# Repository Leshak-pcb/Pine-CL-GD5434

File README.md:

# Pine-CL-GD5434
CL-GD5434-based ISA VGA card.
Tested, works, but may still contain minor errors. Feature connector and 64k rom option are not tested yet.
Notes:
1) R1-R5 are configuration resistors, install R2 & R4 for fast DRAM, R2 & R3 for slow DRAM. Check CL-GD543x databook if you need more info.
2) U10 - optional, provides DD2B support (works with generic PCI BIOS).
3) FB1-F1-D2-C68 - DDC monitor power, remove if not using U10. D2 - BAT54 or equivalent, F1 - 200mA poly fuse.
4) U11 - optional, 93C46 used to store video modes supported by your monitor.
5) U12, U13 - optional, ESD & hot-plug protection.
6) C90-C92 - 10uF - 47uF 6.3V+
7) D1 can be replaced with 1n4148

Creative Commons Attribution-ShareAlike 4.0 International License. See https://creativecommons.org/licenses/by-sa/4.0/.

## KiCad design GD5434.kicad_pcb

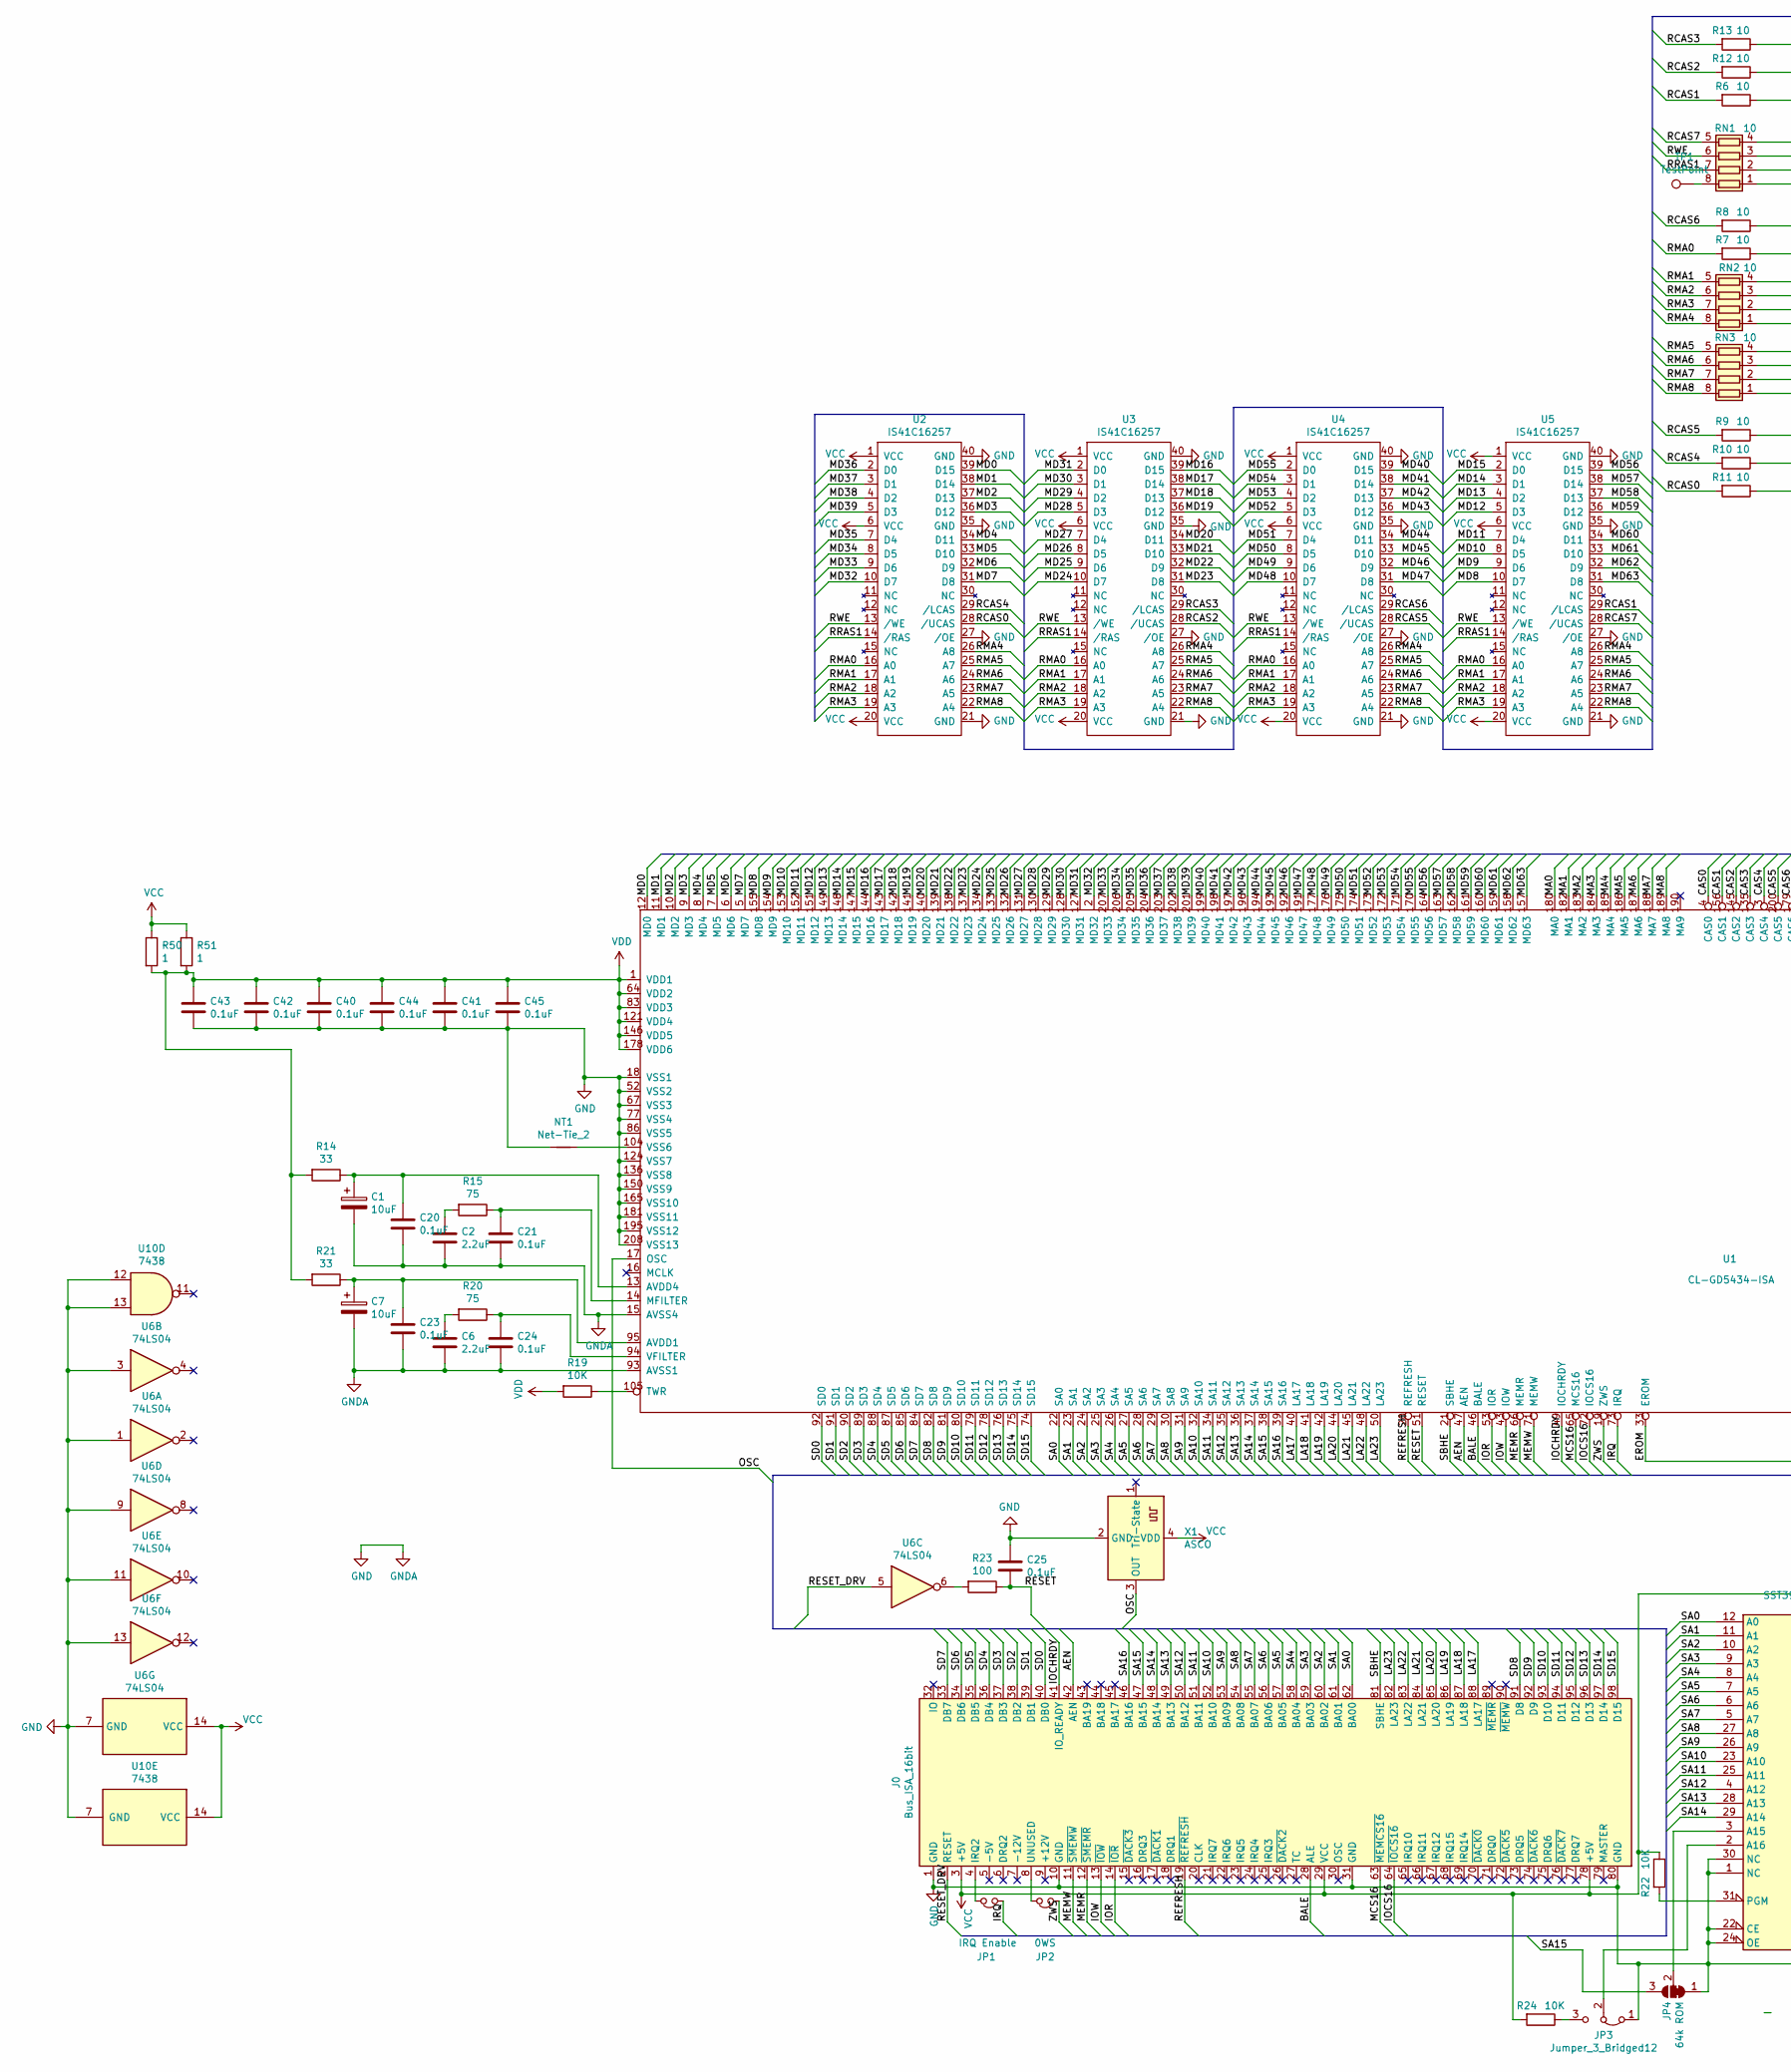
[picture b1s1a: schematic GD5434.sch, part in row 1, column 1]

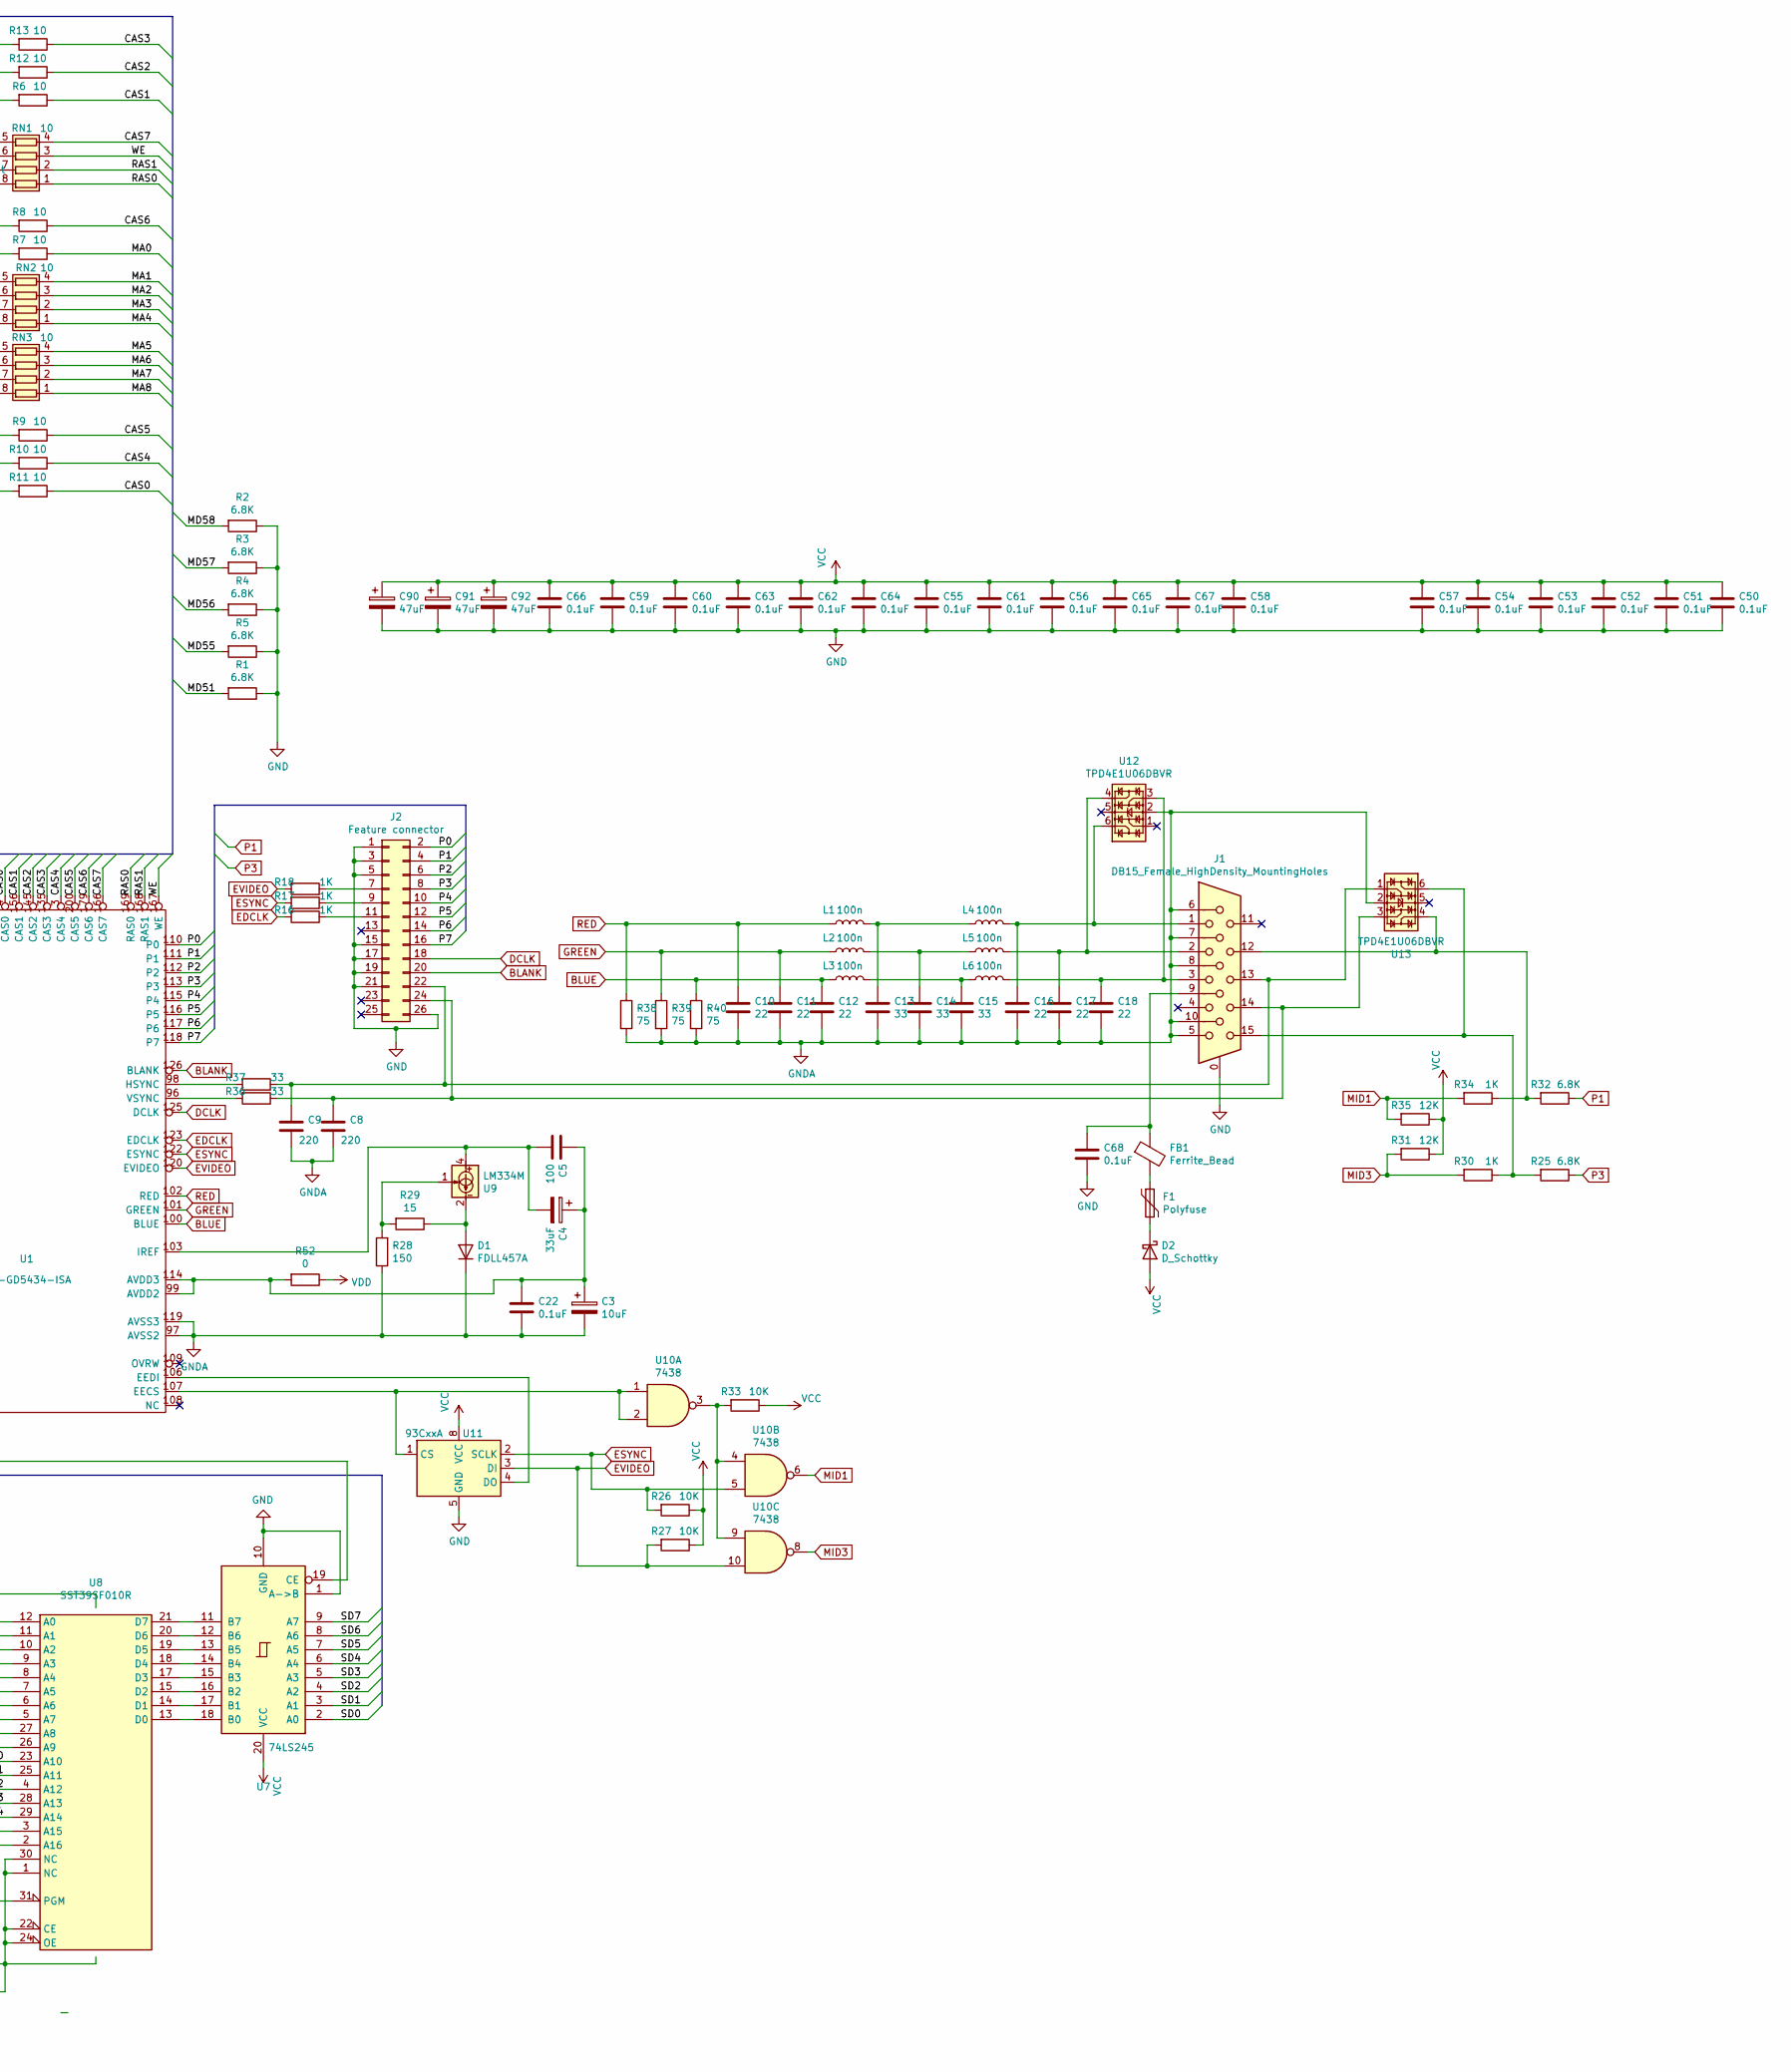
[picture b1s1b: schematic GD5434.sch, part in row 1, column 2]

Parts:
C1, C3, C7: 10uF; CP_Elec_5x5.8
C2, C6: 2.2uF; C_0805_2012Metric_Pad1.15x1.40mm_HandSolder
C4: 33uF; C_Elec_5x5.8
C5: 100; C_0805_2012Metric_Pad1.15x1.40mm_HandSolder
C8, C9: 220; C_0805_2012Metric_Pad1.15x1.40mm_HandSolder
C10, C11, C12, C16, C17, C18: 22; C_0805_2012Metric_Pad1.15x1.40mm_HandSolder
C13, C14, C15: 33; C_0805_2012Metric_Pad1.15x1.40mm_HandSolder
C20, C21, C22, C23, C24, C25, C50, C51, C52, C53, C54, C55, C56, C57, C58, C59, C60, C61, C62, C63, C64, C65, C66, C67, C68: 0.1uF; C_0805_2012Metric_Pad1.15x1.40mm_HandSolder
C40, C41, C42, C43, C44, C45: 0.1uF; C_0603_1608Metric_Pad1.05x0.95mm_HandSolder
C90, C91, C92: 47uF; CP_Radial_D5.0mm_P2.00mm
D1: FDLL457A; D_MiniMELF_Handsoldering
D2: D_Schottky; D_SOT-23_ANK
F1: Polyfuse; Fuse_0805_2012Metric_Pad1.15x1.40mm_HandSolder
FB1: Ferrite_Bead; L_0805_2012Metric_Pad1.15x1.40mm_HandSolder
J0: Bus_ISA_16bit; BUS_AT
J1: DB15_Female_HighDensity_MountingHoles; DSUB-15-HD_Female_Horizontal_P2.29x2.54mm
J2: Feature connector; IDC-Header_2x13_P2.54mm_Vertical
JP1: IRQ Enable; PinHeader_1x02_P2.54mm_Vertical
JP2: 0WS; PinHeader_1x02_P2.54mm_Vertical
JP3: Jumper_3_Bridged12; PinHeader_1x03_P2.54mm_Vertical
JP4: 64k ROM; SolderJumper-3_P1.3mm_Bridged12_RoundedPad1.0x1.5mm_NumberL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
L1, L2, L3, L4, L5, L6: 100n; L_0805_2012Metric_Pad1.15x1.40mm_HandSolder
NT1: Net-Tie_2; NetTie-2_SMD_Pad0.5mm
R1, R2, R3, R4, R5, R25, R32: 6.8K; R_0805_2012Metric_Pad1.15x1.40mm_HandSolder
R6, R9, R10, R11, R12: 10; R_0603_1608Metric_Pad1.05x0.95mm_HandSolder
R7, R8, R13: 10; R_0402_1005Metric
R14, R21, R36, R37: 33; R_0805_2012Metric_Pad1.15x1.40mm_HandSolder
R15, R20, R38, R39, R40: 75; R_0805_2012Metric_Pad1.15x1.40mm_HandSolder
R16, R17, R18, R30, R34: 1K; R_0805_2012Metric_Pad1.15x1.40mm_HandSolder
R19, R22, R24, R26, R27, R33: 10K; R_0805_2012Metric_Pad1.15x1.40mm_HandSolder
R23: 100; R_0805_2012Metric_Pad1.15x1.40mm_HandSolder
R28: 150; R_0805_2012Metric_Pad1.15x1.40mm_HandSolder
R29: 15; R_0805_2012Metric_Pad1.15x1.40mm_HandSolder
R31, R35: 12K; R_0805_2012Metric_Pad1.15x1.40mm_HandSolder
R50, R51: 1; R_1206_3216Metric_Pad1.42x1.75mm_HandSolder
R52: 0; R_0805_2012Metric_Pad1.15x1.40mm_HandSolder
RN1, RN2, RN3: 10; R_Array_Concave_4x0603
TP1: TestPoint; TestPoint_Pad_D1.0mm
U1: CL-GD5434-ISA; PQFP-208_28x28mm_P0.5mm
U2, U3, U4, U5: IS41C16257; SOJ-40-Socket-LongPads
U6: 74LS04; SO-14_5.3x10.2mm_P1.27mm
U7: 74LS245; SOIC-20W_7.5x12.8mm_P1.27mm
U8: SST39SF010R; PLCC-32_THT-Socket
U9: LM334M; SOIC-8_3.9x4.9mm_P1.27mm
U10: 7438; SOIC-14_3.9x8.7mm_P1.27mm
U11: 93CxxA; SOIC-8_3.9x4.9mm_P1.27mm
U12, U13: TPD4E1U06DBVR; SOT-23-6_Handsoldering
X1: ASCO; Oscillator_SMD_Abracon_ASV-4Pin_7.0x5.1mm_HandSoldering

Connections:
/AEN: J0.42 (AEN), U1.47 (AEN)
/BALE: J0.28 (ALE), U1.46 (BALE)
/CAS0: R11.1, U1.4 (CAS0)
/CAS1: R6.1, U1.156 (CAS1)
/CAS2: R12.1, U1.145 (CAS2)
/CAS3: R13.1, U1.135 (CAS3)
/CAS4: R10.1, U1.3 (CAS4)
/CAS5: R9.1, U1.200 (CAS5)
/CAS6: R8.1, U1.179 (CAS6)
/CAS7: RN1.4 (R4.1), U1.166 (CAS7)
/EROM: U1.33 (EROM), U7.19 (CE)
/IOCHRDY: J0.41 (IO_READY), U1.49 (IOCHRDY)
/IOCS16: J0.64 (~IOCS16), U1.72 (IOCS16)
/IOR: J0.14 (~IOR), U1.53 (IOR)
/IOW: J0.13 (~IOW), U1.43 (IOW)
/IRQ: JP1.1, U1.73 (IRQ)
/LA17: J0.88 (LA17), U1.40 (LA17)
/LA18: J0.87 (LA18), U1.41 (LA18)
/LA19: J0.86 (LA19), U1.42 (LA19)
/LA20: J0.85 (LA20), U1.44 (LA20)
/LA21: J0.84 (LA21), U1.45 (LA21)
/LA22: J0.83 (LA22), U1.48 (LA22)
/LA23: J0.82 (LA23), U1.50 (LA23)
/MA0: R7.1, U1.180 (MA0)
/MA1: RN2.4 (R4.1), U1.182 (MA1)
/MA2: RN2.3 (R3.1), U1.183 (MA2)
/MA3: RN2.2 (R2.1), U1.184 (MA3)
/MA4: RN2.1 (R1.1), U1.185 (MA4)
/MA5: RN3.4 (R4.1), U1.186 (MA5)
/MA6: RN3.3 (R3.1), U1.187 (MA6)
/MA7: RN3.2 (R2.1), U1.188 (MA7)
/MA8: RN3.1 (R1.1), U1.189 (MA8)
/MCS16: J0.63 (~MEMCS16), U1.65 (MCS16)
/MD0: U1.12 (MD0), U2.39 (D15)
/MD1: U1.11 (MD1), U2.38 (D14)
/MD2: U1.10 (MD2), U2.37 (D13)
/MD3: U1.9 (MD3), U2.36 (D12)
/MD4: U1.8 (MD4), U2.34 (D11)
/MD5: U1.7 (MD5), U2.33 (D10)
/MD6: U1.6 (MD6), U2.32 (D9)
/MD7: U1.5 (MD7), U2.31 (D8)
/MD8: U1.155 (MD8), U5.10 (D7)
/MD9: U1.154 (MD9), U5.9 (D6)
/MD10: U1.153 (MD10), U5.8 (D5)
/MD11: U1.152 (MD11), U5.7 (D4)
/MD12: U1.151 (MD12), U5.5 (D3)
/MD13: U1.149 (MD13), U5.4 (D2)
/MD14: U1.148 (MD14), U5.3 (D1)
/MD15: U1.147 (MD15), U5.2 (D0)
/MD16: U1.144 (MD16), U3.39 (D15)
/MD17: U1.143 (MD17), U3.38 (D14)
/MD18: U1.142 (MD18), U3.37 (D13)
/MD19: U1.141 (MD19), U3.36 (D12)
/MD20: U1.140 (MD20), U3.34 (D11)
/MD21: U1.139 (MD21), U3.33 (D10)
/MD22: U1.138 (MD22), U3.32 (D9)
/MD23: U1.137 (MD23), U3.31 (D8)
/MD24: U1.134 (MD24), U3.10 (D7)
/MD25: U1.133 (MD25), U3.9 (D6)
/MD26: U1.132 (MD26), U3.8 (D5)
/MD27: U1.131 (MD27), U3.7 (D4)
/MD28: U1.130 (MD28), U3.5 (D3)
/MD29: U1.129 (MD29), U3.4 (D2)
/MD30: U1.128 (MD30), U3.3 (D1)
/MD31: U1.127 (MD31), U3.2 (D0)
/MD32: U1.2 (MD32), U2.10 (D7)
/MD33: U1.207 (MD33), U2.9 (D6)
/MD34: U1.206 (MD34), U2.8 (D5)
/MD35: U1.205 (MD35), U2.7 (D4)
/MD36: U1.204 (MD36), U2.2 (D0)
/MD37: U1.203 (MD37), U2.3 (D1)
/MD38: U1.202 (MD38), U2.4 (D2)
/MD39: U1.201 (MD39), U2.5 (D3)
/MD40: U1.199 (MD40), U4.39 (D15)
/MD41: U1.198 (MD41), U4.38 (D14)
/MD42: U1.197 (MD42), U4.37 (D13)
/MD43: U1.196 (MD43), U4.36 (D12)
/MD44: U1.194 (MD44), U4.34 (D11)
/MD45: U1.193 (MD45), U4.33 (D10)
/MD46: U1.192 (MD46), U4.32 (D9)
/MD47: U1.191 (MD47), U4.31 (D8)
/MD48: U1.177 (MD48), U4.10 (D7)
/MD49: U1.176 (MD49), U4.9 (D6)
/MD50: U1.175 (MD50), U4.8 (D5)
/MD51: R1.2, U1.174 (MD51), U4.7 (D4)
/MD52: U1.173 (MD52), U4.5 (D3)
/MD53: U1.172 (MD53), U4.4 (D2)
/MD54: U1.171 (MD54), U4.3 (D1)
/MD55: R5.2, U1.170 (MD55), U4.2 (D0)
/MD56: R4.2, U1.164 (MD56), U5.39 (D15)
/MD57: R3.2, U1.163 (MD57), U5.38 (D14)
/MD58: R2.2, U1.162 (MD58), U5.37 (D13)
/MD59: U1.161 (MD59), U5.36 (D12)
/MD60: U1.160 (MD60), U5.34 (D11)
/MD61: U1.159 (MD61), U5.33 (D10)
/MD62: U1.158 (MD62), U5.32 (D9)
/MD63: U1.157 (MD63), U5.31 (D8)
/MEMR: J0.12 (~SMEMR), U1.66 (MEMR)
/MEMW: J0.11 (~SMEMW), U1.71 (MEMW)
/OSC: U1.17 (OSC), X1.3 (OUT)
/P0: J2.2, U1.110 (P0)
/P2: J2.6, U1.112 (P2)
/P4: J2.10, U1.115 (P4)
/P5: J2.12, U1.116 (P5)
/P6: J2.14, U1.117 (P6)
/P7: J2.16, U1.118 (P7)
/RAS0: RN1.1 (R1.1), U1.169 (RAS0)
/RAS1: RN1.2 (R2.1), U1.168 (RAS1)
/RCAS0: R11.2, U2.28 (/UCAS)
/RCAS1: R6.2, U5.29 (/LCAS)
/RCAS2: R12.2, U3.28 (/UCAS)
/RCAS3: R13.2, U3.29 (/LCAS)
/RCAS4: R10.2, U2.29 (/LCAS)
/RCAS5: R9.2, U4.28 (/UCAS)
/RCAS6: R8.2, U4.29 (/LCAS)
/RCAS7: RN1.5 (R4.2), U5.28 (/UCAS)
/REFRESH: J0.19 (~REFRESH), U1.20 (REFRESH)
/RESET: C25.2, R23.1, U1.51 (RESET)
/RESET_DRV: J0.2 (RESET), U6.5
/RMA0: R7.2, U2.16 (A0), U3.16 (A0), U4.16 (A0), U5.16 (A0)
/RMA1: RN2.5 (R4.2), U2.17 (A1), U3.17 (A1), U4.17 (A1), U5.17 (A1)
/RMA2: RN2.6 (R3.2), U2.18 (A2), U3.18 (A2), U4.18 (A2), U5.18 (A2)
/RMA3: RN2.7 (R2.2), U2.19 (A3), U3.19 (A3), U4.19 (A3), U5.19 (A3)
/RMA4: RN2.8 (R1.2), U2.26 (A8), U3.26 (A8), U4.26 (A8), U5.26 (A8)
/RMA5: RN3.5 (R4.2), U2.25 (A7), U3.25 (A7), U4.25 (A7), U5.25 (A7)
/RMA6: RN3.6 (R3.2), U2.24 (A6), U3.24 (A6), U4.24 (A6), U5.24 (A6)
/RMA7: RN3.7 (R2.2), U2.23 (A5), U3.23 (A5), U4.23 (A5), U5.23 (A5)
/RMA8: RN3.8 (R1.2), U2.22 (A4), U3.22 (A4), U4.22 (A4), U5.22 (A4)
/RRAS1: RN1.7 (R2.2), U2.14 (/RAS), U3.14 (/RAS), U4.14 (/RAS), U5.14 (/RAS)
/RWE: RN1.6 (R3.2), U2.13 (/WE), U3.13 (/WE), U4.13 (/WE), U5.13 (/WE)
/SA0: J0.62 (BA00), U1.22 (SA0), U8.12 (A0)
/SA1: J0.61 (BA01), U1.23 (SA1), U8.11 (A1)
/SA2: J0.60 (BA02), U1.24 (SA2), U8.10 (A2)
/SA3: J0.59 (BA03), U1.25 (SA3), U8.9 (A3)
/SA4: J0.58 (BA04), U1.26 (SA4), U8.8 (A4)
/SA5: J0.57 (BA05), U1.27 (SA5), U8.7 (A5)
/SA6: J0.56 (BA06), U1.28 (SA6), U8.6 (A6)
/SA7: J0.55 (BA07), U1.29 (SA7), U8.5 (A7)
/SA8: J0.54 (BA08), U1.30 (SA8), U8.27 (A8)
/SA9: J0.53 (BA09), U1.31 (SA9), U8.26 (A9)
/SA10: J0.52 (BA10), U1.32 (SA10), U8.23 (A10)
/SA11: J0.51 (BA11), U1.34 (SA11), U8.25 (A11)
/SA12: J0.50 (BA12), U1.35 (SA12), U8.4 (A12)
/SA13: J0.49 (BA13), U1.36 (SA13), U8.28 (A13)
/SA14: J0.48 (BA14), U1.37 (SA14), U8.29 (A14)
/SA15: J0.47 (BA15), JP4.3 (B), U1.38 (SA15)
/SA16: J0.46 (BA16), U1.39 (SA16)
/SBHE: J0.81 (SBHE), U1.21 (SBHE)
/SD0: J0.40 (DB0), U1.92 (SD0), U7.2 (A0)
/SD1: J0.39 (DB1), U1.91 (SD1), U7.3 (A1)
/SD2: J0.38 (DB2), U1.90 (SD2), U7.4 (A2)
/SD3: J0.37 (DB3), U1.89 (SD3), U7.5 (A3)
/SD4: J0.36 (DB4), U1.88 (SD4), U7.6 (A4)
/SD5: J0.35 (DB5), U1.87 (SD5), U7.7 (A5)
/SD6: J0.34 (DB6), U1.85 (SD6), U7.8 (A6)
/SD7: J0.33 (DB7), U1.84 (SD7), U7.9 (A7)
/SD8: J0.91 (D8), U1.82 (SD8)
/SD9: J0.92 (D9), U1.81 (SD9)
/SD10: J0.93 (D10), U1.80 (SD10)
/SD11: J0.94 (D11), U1.79 (SD11)
/SD12: J0.95 (D12), U1.78 (SD12)
/SD13: J0.96 (D13), U1.76 (SD13)
/SD14: J0.97 (D14), U1.75 (SD14)
/SD15: J0.98 (D15), U1.74 (SD15)
/WE: RN1.3 (R3.1), U1.167 (WE)
/ZWS: JP2.1, U1.19 (ZWS)
BLANK: J2.20, U1.126 (BLANK)
BLUE: C12.1, L3.1, R40.1, U1.100 (BLUE)
DCLK: J2.18, U1.125 (DCLK)
EDCLK: R16.2, U1.123 (EDCLK)
ESYNC: R17.2, R26.2, U1.122 (ESYNC), U10.5, U11.2 (SCLK)
EVIDEO: R18.2, R27.2, U1.120 (EVIDEO), U10.10, U11.3 (DI)
GND: C1.2, C2.2, C3.2, C6.2, C7.2, C8.2, C9.2, C10.2, C11.2, C12.2, C13.2, C14.2, C15.2, C16.2, C17.2, C18.2, C20.2, C21.2, C22.2, C23.2, C24.2, C25.1, C40.2, C41.2, C42.2, C43.2, C44.2, C45.2, C50.2, C51.2, C52.2, C53.2, C54.2, C55.2, C56.2, C57.2, C58.2, C59.2, C60.2, C61.2, C62.2, C63.2, C64.2, C65.2, C66.2, C67.2, C68.2, C90.2, C91.2, C92.2, D1.1 (K), J0.1 (GND), J0.10 (GND), J0.31 (GND), J0.80 (GND), J1.0, J1.5, J1.6, J1.7, J1.8, J1.10, J2.1, J2.3, J2.5, J2.15, J2.17, J2.19, J2.21, J2.26, JP3.1 (A), JP4.1 (A), NT1.1, R1.1, R2.1, R3.1, R4.1, R5.1, R28.1, R38.2, R39.2, R40.2, U1.15 (AVSS4), U1.18 (VSS1), U1.52 (VSS2), U1.67 (VSS3), U1.77 (VSS4), U1.86 (VSS5), U1.93 (AVSS1), U1.97 (AVSS2), U1.119 (AVSS3), U1.124 (VSS7), U1.136 (VSS8), U1.150 (VSS9), U1.165 (VSS10), U1.181 (VSS11), U1.195 (VSS12), U1.208 (VSS13), U2.21 (GND), U2.27 (/OE), U2.35 (GND), U2.40 (GND), U3.21 (GND), U3.27 (/OE), U3.35 (GND), U3.40 (GND), U4.21 (GND), U4.27 (/OE), U4.35 (GND), U4.40 (GND), U5.21 (GND), U5.27 (/OE), U5.35 (GND), U5.40 (GND), U6.1, U6.3, U6.7 (GND), U6.9, U6.11, U6.13, U7.1 (A->B), U7.10 (GND), U8.1 (NC), U8.16 (GND), U8.22 (CE), U8.24 (OE), U8.30 (NC), U10.7 (GND), U10.12, U10.13, U11.5 (GND), U12.2, U13.2, X1.2 (GND)
GREEN: C11.1, L2.1, R39.1, U1.101 (GREEN)
MID1: R34.2, R35.2, U10.6
MID3: R30.2, R31.2, U10.8
unnamed: C1.1, C20.1, R14.1, U1.13 (AVDD4)
unnamed: C2.1, R15.2
unnamed: C4.2, C5.2, U1.103 (IREF), U9.4
unnamed: C6.1, R20.2
unnamed: C8.1, J1.14, J2.24, R36.1, U13.3
unnamed: C9.1, J1.13, J2.22, R37.1, U13.1
unnamed: C13.1, L1.2, L4.1
unnamed: C14.1, L2.2, L5.1
unnamed: C15.1, L3.2, L6.1
unnamed: C16.1, J1.1, L4.2, U12.6
unnamed: C17.1, J1.2, L5.2, U12.4
unnamed: C18.1, J1.3, L6.2, U12.3
unnamed: C21.1, R15.1, U1.14 (MFILTER)
unnamed: C3.1, C4.1, C5.1, C22.1, R52.2, U1.99 (AVDD2), U1.114 (AVDD3)
unnamed: C7.1, C23.1, R21.1, U1.95 (AVDD1)
unnamed: C24.1, R20.1, U1.94 (VFILTER)
unnamed: C68.1, FB1.1, J1.9
unnamed: D1.2 (A), R29.1, U9.2, U9.3, U9.6, U9.7
unnamed: D2.1 (K), F1.2
unnamed: F1.1, FB1.2
unnamed: J0.4 (IRQ2), JP1.2
unnamed: J0.8 (UNUSED), JP2.2
unnamed: J1.12, R32.2, R34.1, U13.4
unnamed: J1.15, R25.2, R30.1, U13.6
unnamed: J2.7, R18.1
unnamed: J2.9, R17.1
unnamed: J2.11, R16.1
unnamed: JP3.2 (C), U8.2 (A16)
unnamed: JP3.3 (B), R24.1
unnamed: JP4.2 (C), U8.3 (A15)
unnamed: NT1.2, U1.104 (VSS6)
unnamed: R19.1, U1.105 (TWR)
unnamed: R22.2, U8.31 (PGM)
unnamed: R23.2, U6.6
unnamed: R28.2, R29.2, U9.1
unnamed: R33.2, U10.3, U10.4, U10.9
unnamed: R36.2, U1.96 (VSYNC)
unnamed: R37.2, U1.98 (HSYNC)
unnamed: RN1.8 (R1.2), TP1.1
unnamed: U1.106 (EEDI), U11.4 (DO)
unnamed: U1.107 (EECS), U10.1, U10.2, U11.1 (CS)
unnamed: U7.11 (B7), U8.21 (D7)
unnamed: U7.12 (B6), U8.20 (D6)
unnamed: U7.13 (B5), U8.19 (D5)
unnamed: U7.14 (B4), U8.18 (D4)
unnamed: U7.15 (B3), U8.17 (D3)
unnamed: U7.16 (B2), U8.15 (D2)
unnamed: U7.17 (B1), U8.14 (D1)
unnamed: U7.18 (B0), U8.13 (D0)
P1: J2.4, R32.1, U1.111 (P1)
P3: J2.8, R25.1, U1.113 (P3)
RED: C10.1, L1.1, R38.1, U1.102 (RED)
VCC: C50.1, C51.1, C52.1, C53.1, C54.1, C55.1, C56.1, C57.1, C58.1, C59.1, C60.1, C61.1, C62.1, C63.1, C64.1, C65.1, C66.1, C67.1, C90.1, C91.1, C92.1, D2.2 (A), J0.3 (+5V), J0.29 (VCC), J0.78 (+5V), R22.1, R24.2, R26.1, R27.1, R31.1, R33.1, R35.1, R50.1, R51.1, U2.1 (VCC), U2.6 (VCC), U2.20 (VCC), U3.1 (VCC), U3.6 (VCC), U3.20 (VCC), U4.1 (VCC), U4.6 (VCC), U4.20 (VCC), U5.1 (VCC), U5.6 (VCC), U5.20 (VCC), U6.14 (VCC), U7.20 (VCC), U8.32 (VCC), U10.14 (VCC), U11.8 (VCC), X1.4 (VDD)
VDD: C40.1, C41.1, C42.1, C43.1, C44.1, C45.1, R14.2, R19.2, R21.2, R50.2, R51.2, R52.1, U1.1 (VDD1), U1.64 (VDD2), U1.83 (VDD3), U1.121 (VDD4), U1.146 (VDD5), U1.178 (VDD6)

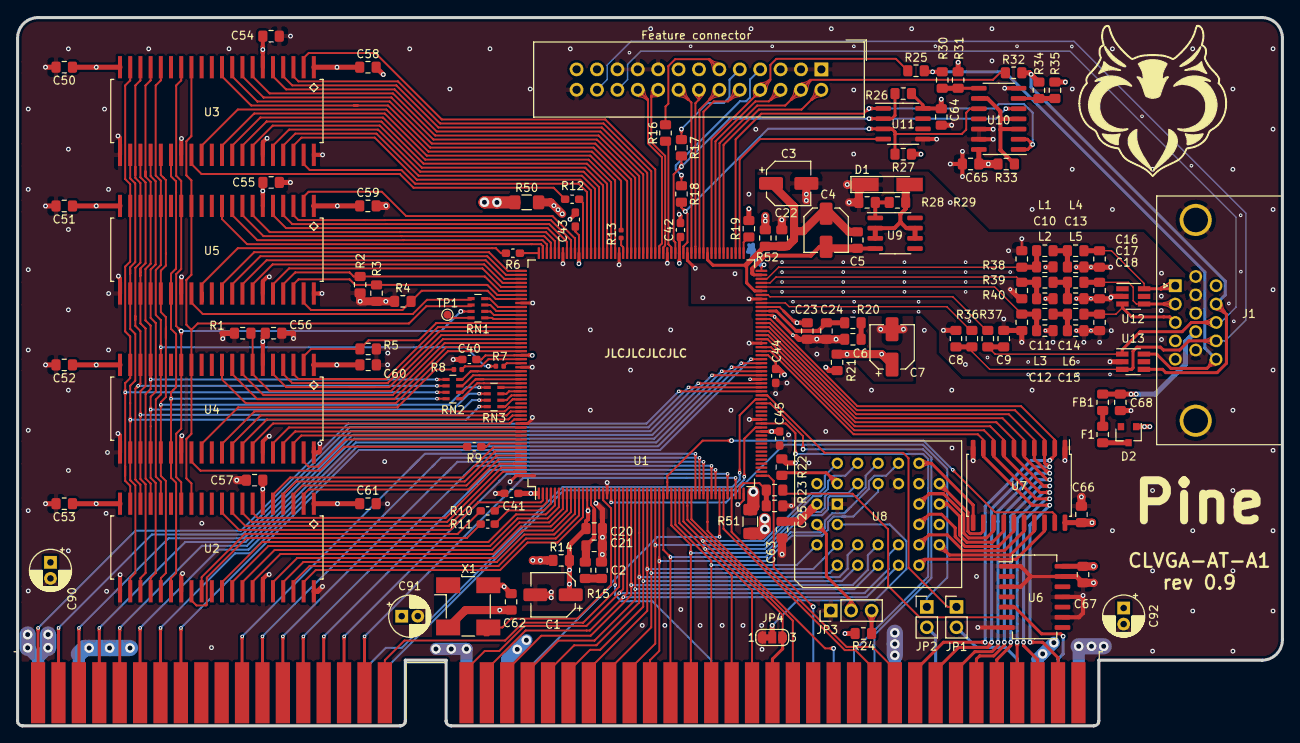
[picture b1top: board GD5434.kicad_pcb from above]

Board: 4 copper layers, 157.5 x 88.2 mm, 131 parts (1 on the bottom side), 230 nets.

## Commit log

2020-07-05 Add files via upload
    V0.9 PCB & schematics
2020-07-07 Add files via upload
    fixed 74LS245 connections
2020-09-13 Add files via upload
    Few updates + BOM
2020-09-13 Add files via upload
    add photo
